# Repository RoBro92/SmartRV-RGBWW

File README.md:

# SmartRV RGBWW Controller
**A ESP32 based RGBWW controller**

All feature requests are tracked in the GitHub issue tracker. 
[Feature Requests](https://github.com/RoBro92/feature-requests/issues)

This RGBWW control board has been designed to allow smart control of an attached LED strip. It supports 5 seperate channels that are switched via N Channel Mosfets, this is sutiable for the majority of LV LED devices. It is designed to integrate with a home automation system such as Home Assistant, though can operate standalone via an access point.

The module has been kept as compact as possible and allows for a direct connection to 12v or 24v vehicle systems. 

**If you want to support the development you can purchase this board as a DIY kit or assembled from my Ko-Fi Shop [SmartRV Shop](https://ko-fi.com/smartrv/shop)**

# **v0.1**
This is the pre-production initial design files with planned features and initial designs. Design is as far untested.

# **New This Release**

- [x] Upload full Kicad files

# **Current Features**
- [x] ESP32 Microcontroller
- [x] Serperate 5 channel LED control 1a per channel
- [x] Reverse voltage protection
- [x] FTDI programmer pinout
- [x] 12v input

# **Upcoming Changes**
- [ ] On board programming
- [ ] Bluetooth connection to hub

# **Images**
<table>
  <tr>
    <td>3D Model</td>
     <td>PCB Schematic</td>
  </tr>
  <tr>
    <td></td>
    <td></td>
  </tr>
 </table>
 
 <table>
  <tr>
    <td>PCB Layout</td>
  </tr>
  <tr>
    <td></td>
  </tr>
 </table>

# **WARNING**
This board does not have any fuse protection as such this must be provided externally.# SmartRV-RGBWW

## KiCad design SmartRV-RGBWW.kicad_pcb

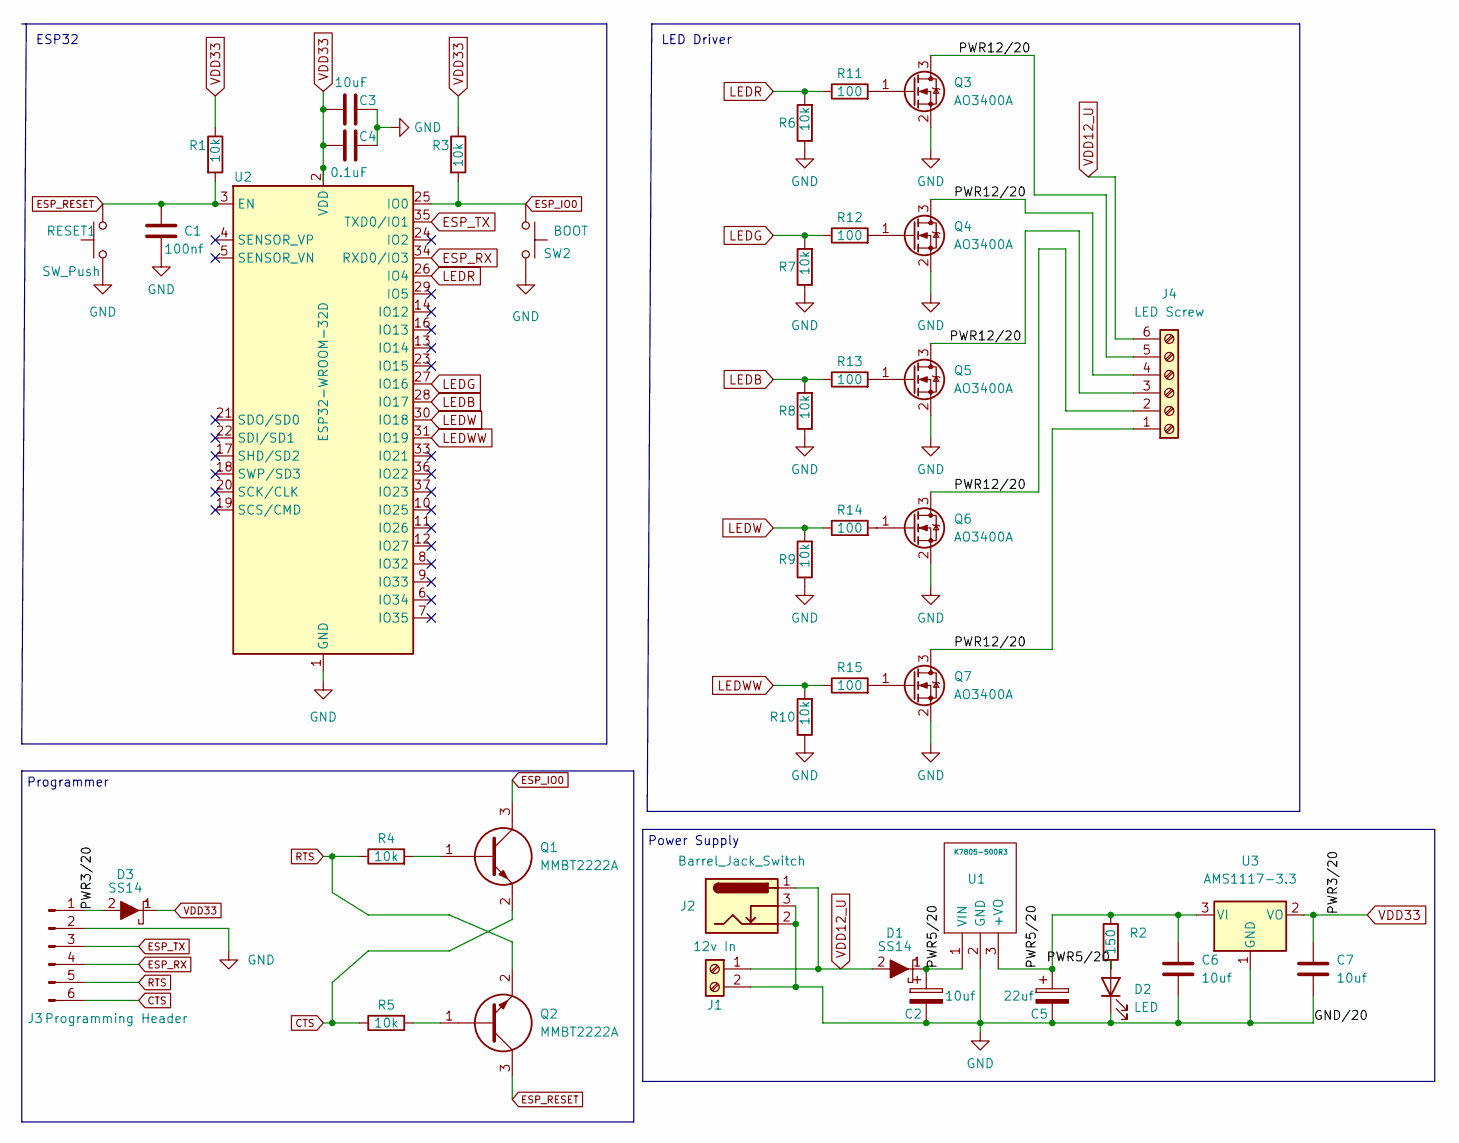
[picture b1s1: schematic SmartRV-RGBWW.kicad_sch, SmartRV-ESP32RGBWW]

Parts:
C1: 100nf; C_0805_2012Metric
C2, C6, C7: 10uf; C_0805_2012Metric
C3: 10uF; C_0805_2012Metric
C4: 0.1uF; C_0805_2012Metric
C5: 22uf; C_0805_2012Metric
D1, D3: SS14; DIOM5126X250N; Manufacturer_Part_Number SS14; Mouser Part Number 821-SS14
D2: LED; LED_D3.0mm; Fwd Voltage 2-2.2
J1: 12v In; TerminalBlock_Phoenix_MKDS-1,5-2_1x02_P5.00mm_Horizontal
J2: Barrel_Jack_Switch; BarrelJack_Wuerth_6941xx301002
J3: Programming Header; PinHeader_1x06_P2.54mm_Vertical
J4: LED Screw; TerminalBlock_Phoenix_MKDS-1,5-6_1x06_P5.00mm_Horizontal
Q1, Q2: MMBT2222A; SOT95P240X120-3N; Manufacturer_Part_Number MMBT2222A; Mouser Part Number 512-MMBT2222A
Q3, Q4, Q5, Q6, Q7: AO3400A; SOT-23
R1, R3, R4, R5, R6, R7, R8, R9, R10: 10k; R_0805_2012Metric
R2: 150; R_0805_2012Metric
R11, R12, R13, R14, R15: 100; R_0805_2012Metric
RESET1: SW_Push; SW_PUSH_6mm
SW2: BOOT; SW_PUSH_6mm
U1: K7805-500R3; K7805500R3; Manufacturer_Part_Number K7805-500R3
U2: ESP32-WROOM-32D; ESP32-WROOM-32
U3: AMS1117-3.3; SOT-223-3_TabPin2

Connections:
/PWR5/20: C2.1, C5.1, C6.1, D1.1, D2.2 (A), R2.1, R2.2, U1.1 (VIN), U1.3 (+VO), U3.3 (VI)
/PWR12/20: J4.1, J4.2, J4.3, J4.4, J4.5, Q3.3 (D), Q4.3 (D), Q5.3 (D), Q6.3 (D), Q7.3 (D)
CTS: J3.6, Q1.2, R5.1
ESP_IO0: Q1.3, R3.2, SW2.1, U2.25 (IO0); also elsewhere on the board
ESP_RESET: C1.2, Q2.3, R1.2, RESET1.2, U2.3 (EN); also elsewhere on the board
ESP_RX: J3.4, U2.34 (RXD0/IO3)
ESP_TX: J3.3, U2.35 (TXD0/IO1)
GND: C1.1, C2.2, C3.2, C4.2, C5.2, C6.2, C7.2, D2.1 (K), J1.2, J2.2, J2.3, J3.2, Q3.2 (S), Q4.2 (S), Q5.2 (S), Q6.2 (S), Q7.2 (S), R6.1, R7.1, R8.1, R9.1, R10.1, RESET1.1, SW2.2, U1.2 (GND), U2.1 (GND), U2.15 (GND), U2.38 (GND), U2.39 (GND), U3.1 (GND); also elsewhere on the board
LEDB: R8.2, R13.1, U2.28 (IO17)
LEDG: R7.2, R12.1, U2.27 (IO16)
LEDR: R6.2, R11.1, U2.26 (IO4)
LEDW: R9.2, R14.1, U2.30 (IO18)
LEDWW: R10.2, R15.1, U2.31 (IO19)
unnamed: Q1.1, R4.2
unnamed: Q2.1, R5.2
unnamed: Q3.1 (G), R11.2
unnamed: Q4.1 (G), R12.2
unnamed: Q5.1 (G), R13.2
unnamed: Q6.1 (G), R14.2
unnamed: Q7.1 (G), R15.2
RTS: J3.5, Q2.2, R4.1
VDD12_U: D1.2, J1.1, J2.1, J4.6
VDD33: C3.1, C4.1, C7.1, D3.1, D3.2, J3.1, R1.1, R3.1, U2.2 (VDD), U3.2 (VO)

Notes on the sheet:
ESP32
Power Supply
Programmer
LED Driver

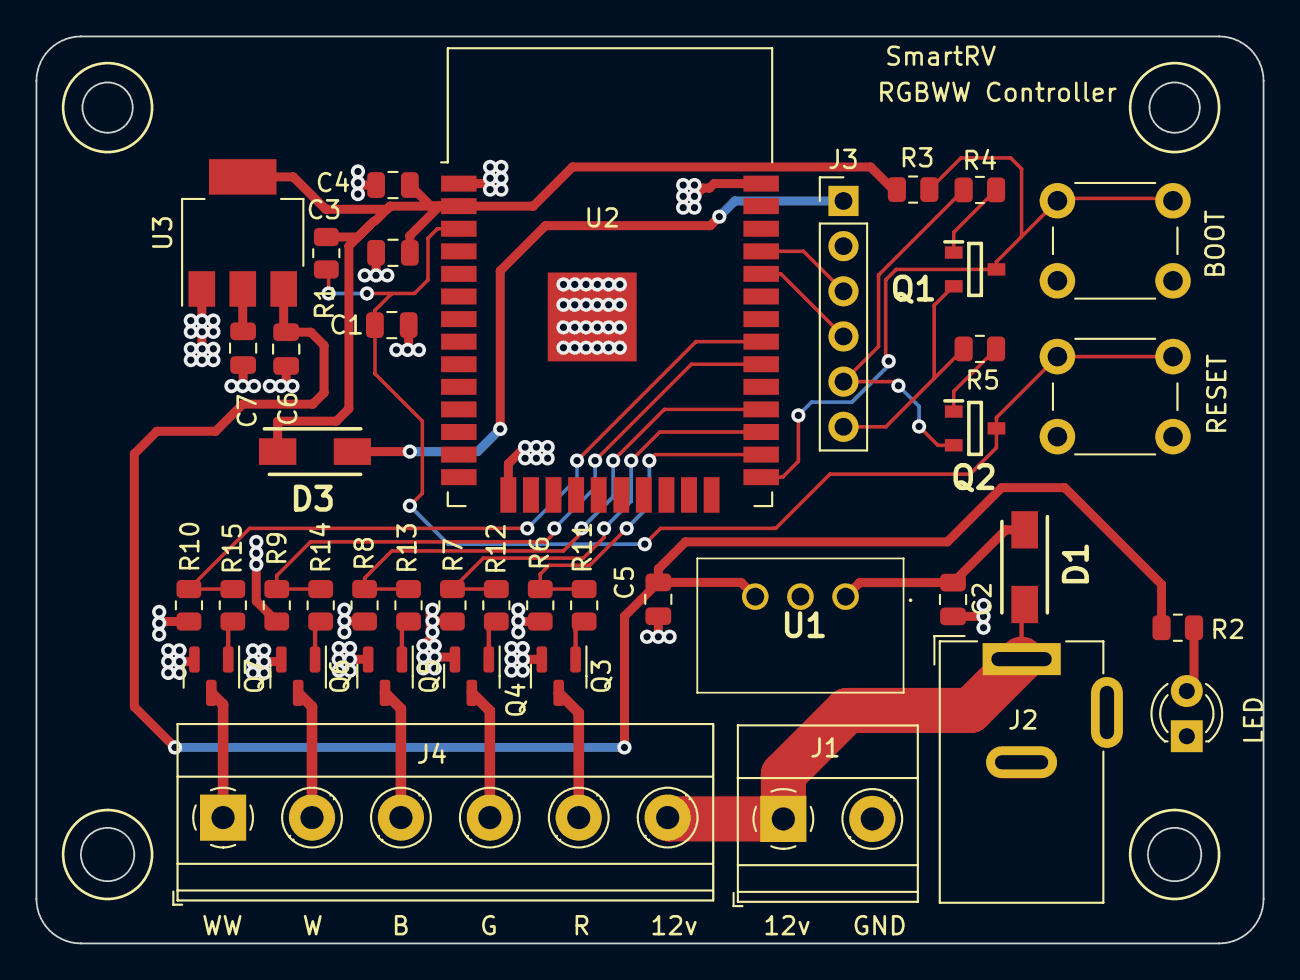
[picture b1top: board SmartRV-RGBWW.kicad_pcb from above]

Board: 2 copper layers, 69.0 x 51.0 mm, 41 parts (0 on the bottom side), 23 nets.

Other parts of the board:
BOOT: SW_Push; SW_PUSH_6mm
RESET: SW_Push; SW_PUSH_6mm

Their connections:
ESP_IO0: BOOT.1; also elsewhere on the board
ESP_RESET: RESET.2; also elsewhere on the board
GND: BOOT.2, RESET.1; also elsewhere on the board

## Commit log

2022-02-19 Added Image files and PCB/Schematic
2022-02-19 added Schematic and PCB files
